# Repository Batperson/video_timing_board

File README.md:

# Video Timing Board
A Development board to extract timing and subcarrier signals from a composite PAL or NTSC video source.

This is part of my ongoing project to develop a system to superimpose colour text and graphics from a microcontroller onto a composite TV signal. My earlier experimenter's board which can be found at https://github.com/Batperson/video_experimenters_board used a high-speed digital decoder and encoder connected back-to-back, but I now want to try some different methods.

One method is to use an AD724 chip from Analog Devices to generate composite video from RGB signals supplied by a microcontroller. If the AD724 is driven by a clock synchronised with an incoming video signal's colour subcarrier, then its output will also be synchronised with that same subcarrier (i.e. genlocked). Then, a fast switch can be used to switch between the incoming video signal and the text/graphic video signal which we wish to superimpose.

Another method is to generate composite video directly from a microcontroller using the SPI output. Rossum at https://rossumblog.com/2010/06/10/rbox-a-diy-32-bit-game-console-for-the-price-of-a-latte/ has already demonstrated this with the most impressive RBox, a game console based on the Arm Cortex M0 which generates full-colour composite video without any supporting ICs. My theory is that I can do the same, but supply an external clock to the SPI. If this clock is derived from an incoming video signal's colourburst then the output should be genlocked..

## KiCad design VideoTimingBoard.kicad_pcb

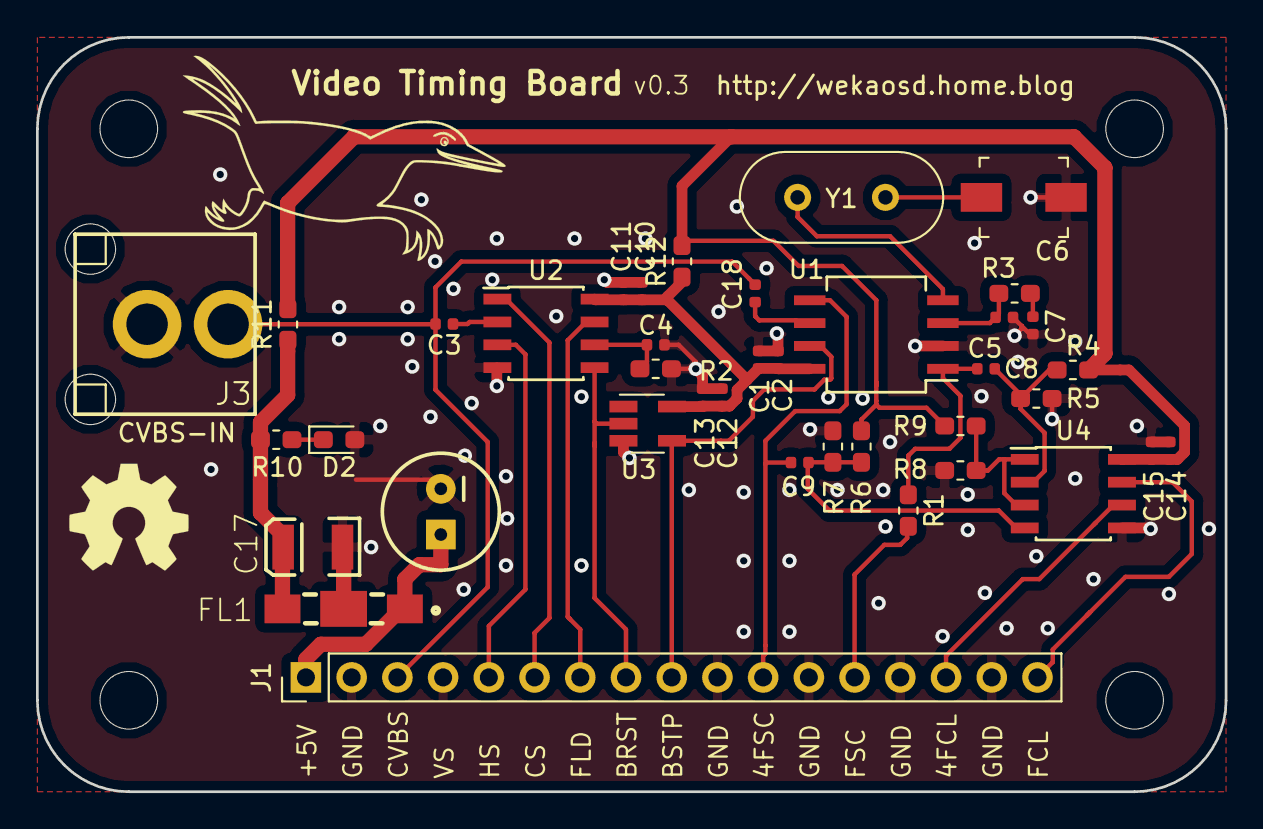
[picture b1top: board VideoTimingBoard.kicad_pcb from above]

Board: 2 copper layers, 66.0 x 41.9 mm, 39 parts (0 on the bottom side), 25 nets.

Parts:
C1, C10, C12, C14: 10uF; C_0402_1005Metric
C2, C3, C4, C7, C11, C13, C15, C18: 0.1uF; C_0402_1005Metric
C5: 470pF; C_0402_1005Metric
C6: 5-25pF; C_Trimmer_Murata_TZB4-A
C8, C9: 1nF; C_0402_1005Metric
C16: 220uF; CPOL-RADIAL
C17: 33uF; EIA3528
D2: LED_0603_1608Metric_Pad1.05x0.95mm_HandSolder
FL1: NFE61PT472C1H9L; 6816
J1: PinHeader_1x17_P2.54mm_Vertical
J3: RCA
R1, R11: 0R; R_0603_1608Metric_Pad1.05x0.95mm_HandSolder
R2: 680K; R_0603_1608Metric_Pad1.05x0.95mm_HandSolder
R3: 47K; R_0603_1608Metric_Pad1.05x0.95mm_HandSolder
R4, R5, R6, R7, R8, R9: 10K; R_0603_1608Metric_Pad1.05x0.95mm_HandSolder
R10: 150R; R_0603_1608Metric_Pad1.05x0.95mm_HandSolder
R12: R0; R_0603_1608Metric_Pad1.05x0.95mm_HandSolder
U1: MC44144; SO-8_5.3x6.2mm_P1.27mm
U2: LM1881; SOIC-8_3.9x4.9mm_P1.27mm
U3: SN74LVC1GU04; SOT-23-5_HandSoldering
U4: TLV3502; SOIC-8_3.9x4.9mm_P1.27mm
Y1: Crystal_HC49-U_Vertical

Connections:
+5V: C16.1, FL1.1, J1.1
/4FCLK: J1.15, U4.6
/4FSC: C9.2, J1.11, U1.5
/4FSC-BIAS: C9.1, R6.2, R7.1, U4.4
/BURST: J1.8, U2.5, U3.2
/BURST-INV: J1.9, U1.7, U3.4
/CSYNC: J1.6, U2.1
/CVBS: C3.2, C18.1, J1.3, J3.1
/FCLK: J1.17, U4.7
/FIELD: J1.7, U2.7
/FSC: C8.2, R1.1, U1.1
/FSC1: J1.13, R1.2
/FSC-BIAS: C8.1, R4.2, R5.1, U4.2
/VSYNC: J1.5, U2.3
/XTAL: U1.4, Y1.2
GND: C1.2, C2.2, C4.2, C5.1, C6.1, C7.1, C10.2, C11.1, C12.2, C13.2, C14.1, C15.1, C16.2, C17.2, D2.1, FL1.2, J1.2, J1.4, J1.10, J1.12, J1.14, J1.16, J3.2, R2.2, R5.2, R7.2, R8.1, U1.2, U2.4, U3.3, U4.5
unnamed: C3.1, U2.2
unnamed: C4.1, R2.1, U2.6
unnamed: C5.2, R3.2, U1.3
unnamed: C6.2, Y1.1
unnamed: C7.2, R3.1
unnamed: C18.2, U1.6
unnamed: D2.2, R10.2
unnamed: R8.2, R9.1, U4.1, U4.3
VDD: C1.1, C2.1, C10.1, C11.2, C12.1, C13.1, C14.2, C15.2, C17.1, FL1.3, R4.1, R6.1, R9.2, R10.1, R11.1, R11.2, R12.1, R12.2, U1.8, U2.8, U3.5, U4.8

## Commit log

2019-04-05 Design complete.
2019-08-30 Changed .05" pinheaders to .1" Removed CVBS clamp The MC44144 and LM1881 are separately AC-coupled to the CVBS signal.
2019-08-31 Changed jumpers
